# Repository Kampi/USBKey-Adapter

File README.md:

# USBKeyAdater

## Table of Contents

- [USBKeyAdater](#usbkeyadater)
  - [Table of Contents](#table-of-contents)
  - [About](#about)
  - [Pinout](#pinout)
  - [History](#history)
  - [Maintainer](#maintainer)

## About

Breadboard adapter for the [AT90USBKEY](https://www.microchip.com/DevelopmentTools/ProductDetails/PartNO/AT90USBKEY2) development board.

> You can use [these](https://www.mouser.de/ProductDetail/Harwin/M52-5100545?qs=%2Fha2pyFaduhO%252BEepM1RQNXq7MdGdl0xmqxrysd7ByKdGvk59s6yMfA%3D%3D) headers to attach the `AT90USBKey` with the adapter.

Please write an e-mail to [DanielKampert@kampis-elektroecke.de](DanielKampert@kampis-elektroecke.de) if you have any questions.

## Pinout

| **Adapter** | **Microcontroller**              |
|:-----------:|:--------------------------------:|
| 1           | A.7                              |
| 2           | A.6                              |
| 3           | A.5                              |
| 4           | A.4                              |
| 5           | A.3                              |
| 6           | A.2                              |
| 7           | A.1                              |
| 8           | A.0                              |
| 9           | B.7                              |
| 10          | B.6                              |
| 11          | B.5                              |
| 12          | B.4                              |
| 13          | B.3                              |
| 14          | B.2                              |
| 15          | B.1                              |
| 16          | B.0                              |
| 17          | C.7                              |
| 18          | C.6                              |
| 19          | C.5                              |
| 20          | C.4                              |
| 21          | C.3                              |
| 22          | C.2                              |
| 23          | C.1                              |
| 24          | C.0                              |
| 25          | GND                              |
| 26          | D.0                              |
| 27          | D.1                              |
| 28          | D.2                              |
| 29          | D.3                              |
| 30          | D.4                              |
| 31          | D.5                              |
| 32          | D.6                              |
| 33          | D.7                              |
| 34          | E.0                              |
| 35          | E.1                              |
| 36          | E.2                              |
| 37          | E.3                              |
| 38          | E.4                              |
| 39          | E.5                              |
| 40          | E.6                              |
| 41          | E.7                              |
| 42          | F.0                              |
| 43          | F.1                              |
| 44          | F.2                              |
| 45          | F.3                              |
| 46          | F.4                              |
| 47          | F.5                              |
| 48          | F.6                              |
| 49          | F.7                              |
| 50          | Vcc                              |

## History

| **Version**  | **Description**                            | **Date**   |
|:------------:|:------------------------------------------:|:----------:|
| 1.0          | First release                              | 04.01.2020 |

## Maintainer

- [Daniel Kampert](mailto:DanielKampert@kampis-elektroecke.de)

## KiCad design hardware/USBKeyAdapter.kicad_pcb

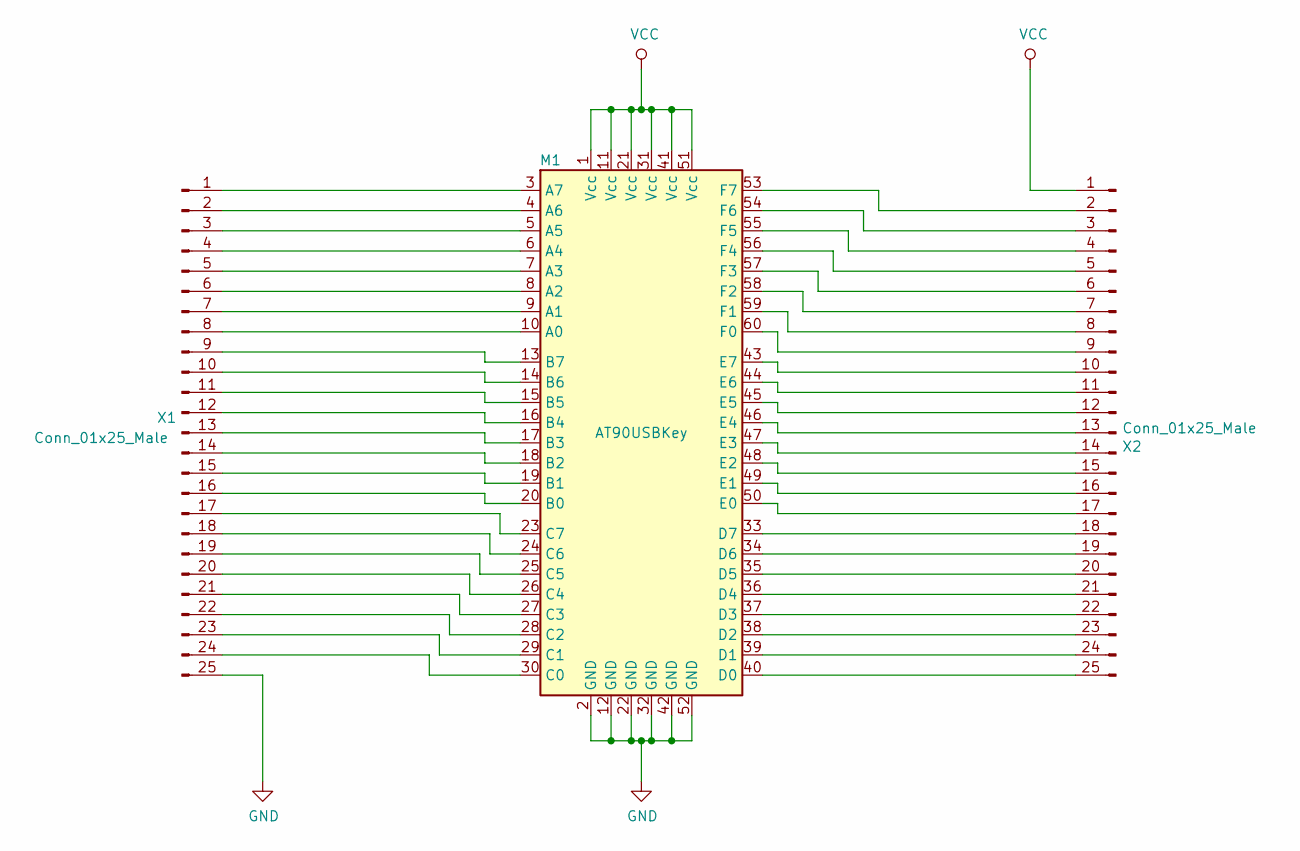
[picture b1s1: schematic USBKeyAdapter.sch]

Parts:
M1: AT90USBKey
X1, X2: Conn_01x25_Male; PinHeader_1x25_P2.54mm_Vertical; Mouser 855-M20-9992545

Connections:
GND: M1.2 (GND), M1.12 (GND), M1.22 (GND), M1.32 (GND), M1.42 (GND), M1.52 (GND), X1.25
unnamed: M1.3 (A7), X1.1
unnamed: M1.4 (A6), X1.2
unnamed: M1.5 (A5), X1.3
unnamed: M1.6 (A4), X1.4
unnamed: M1.7 (A3), X1.5
unnamed: M1.8 (A2), X1.6
unnamed: M1.9 (A1), X1.7
unnamed: M1.10 (A0), X1.8
unnamed: M1.13 (B7), X1.9
unnamed: M1.14 (B6), X1.10
unnamed: M1.15 (B5), X1.11
unnamed: M1.16 (B4), X1.12
unnamed: M1.17 (B3), X1.13
unnamed: M1.18 (B2), X1.14
unnamed: M1.19 (B1), X1.15
unnamed: M1.20 (B0), X1.16
unnamed: M1.23 (C7), X1.17
unnamed: M1.24 (C6), X1.18
unnamed: M1.25 (C5), X1.19
unnamed: M1.26 (C4), X1.20
unnamed: M1.27 (C3), X1.21
unnamed: M1.28 (C2), X1.22
unnamed: M1.29 (C1), X1.23
unnamed: M1.30 (C0), X1.24
unnamed: M1.33 (D7), X2.18
unnamed: M1.34 (D6), X2.19
unnamed: M1.35 (D5), X2.20
unnamed: M1.36 (D4), X2.21
unnamed: M1.37 (D3), X2.22
unnamed: M1.38 (D2), X2.23
unnamed: M1.39 (D1), X2.24
unnamed: M1.40 (D0), X2.25
unnamed: M1.43 (E7), X2.10
unnamed: M1.44 (E6), X2.11
unnamed: M1.45 (E5), X2.12
unnamed: M1.46 (E4), X2.13
unnamed: M1.47 (E3), X2.14
unnamed: M1.48 (E2), X2.15
unnamed: M1.49 (E1), X2.16
unnamed: M1.50 (E0), X2.17
unnamed: M1.53 (F7), X2.2
unnamed: M1.54 (F6), X2.3
unnamed: M1.55 (F5), X2.4
unnamed: M1.56 (F4), X2.5
unnamed: M1.57 (F3), X2.6
unnamed: M1.58 (F2), X2.7
unnamed: M1.59 (F1), X2.8
unnamed: M1.60 (F0), X2.9
VCC: M1.1 (Vcc), M1.11 (Vcc), M1.21 (Vcc), M1.31 (Vcc), M1.41 (Vcc), M1.51 (Vcc), X2.1

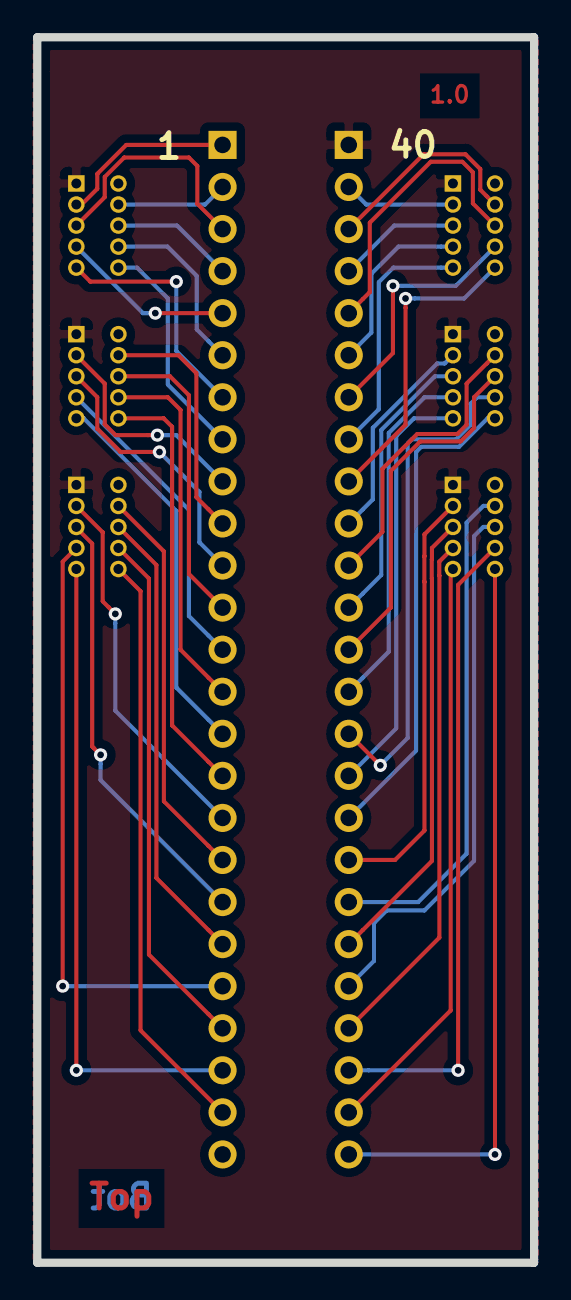
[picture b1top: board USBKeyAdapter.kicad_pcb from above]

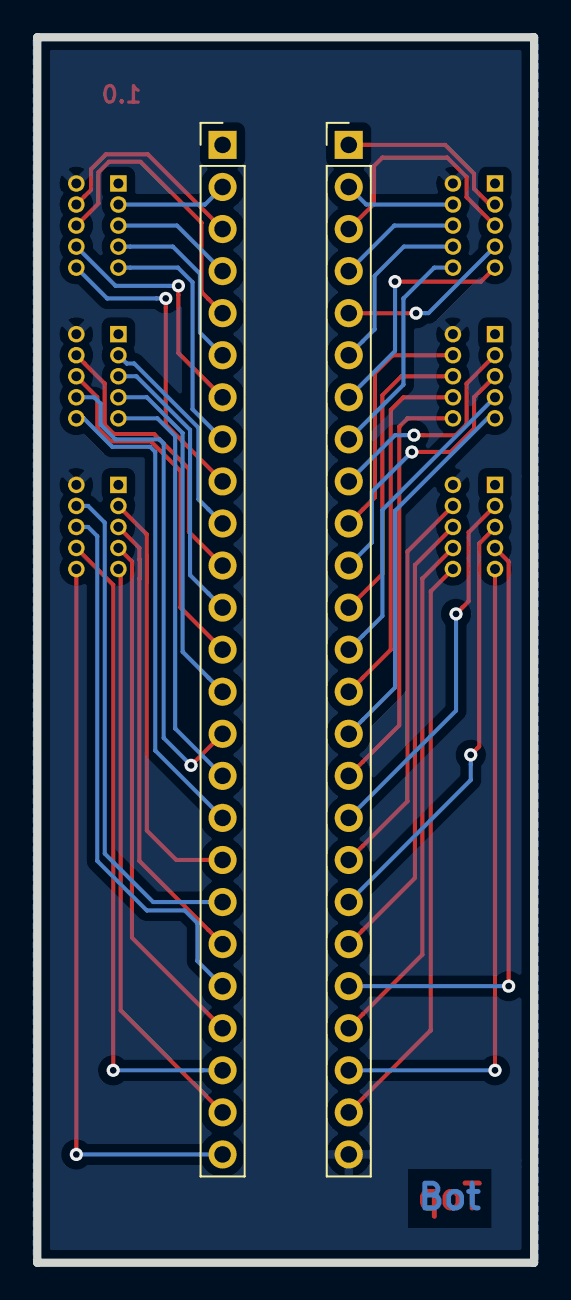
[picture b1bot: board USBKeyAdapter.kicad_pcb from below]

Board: 2 copper layers, 30.0 x 74.0 mm, 3 parts (2 on the bottom side), 50 nets.

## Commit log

2020-01-04 First hardware release
2020-01-13 First release
2020-02-09 Fix wrong email address in README
2020-04-22 Update LICENSE
